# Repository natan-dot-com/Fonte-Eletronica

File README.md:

# Fonte de Tensão Variável (12V-3V)
## Introdução
Projeto para a aula de Eletrônica para Computação (SSC0180), no ICMC/USP-São Carlos, ministrada pelo docente [Eduardo Simões](https://gitlab.com/simoesusp).
O projeto consiste numa fonte de alimentação de tensão variável, feita num simulador com o uso de resistores, diodos, capacitores, transformadores e um regulador de tensão.

O circuito fora feito pelo grupo 9 de 2020/1:  
- [Natan Sanches](https://github.com/natan-dot-com);  
- [Gabriel Vicente Rodrigues](https://github.com/gabriel-vr);  
- [Lucas Mihara](https://github.com/lucasmihara);  
- [Vitor Beneti Martins](https://github.com/benetche).  

Projeto indexado ao [Gitlab](https://gitlab.com/simoesusp/disciplinas/-/tree/master/SSC0180-Eletronica-para-Computacao).

## Sobre o projeto
O projeto, por medidas de restrição social, fora feito em dois simuladores de circuitos elétricos: no [Falstad](http://tinyurl.com/y9k5xbtm), online, e no Eagle, outro simulador mais completo que também executa a impressão da placa de circuito final. As imagens e o arquivo do projeto estão contidos neste repositório e a seguir.  
Houve também a produção de um [vídeo explicativo](https://youtu.be/nBSvIfqxYiY) acerca do projeto, que complementará a leitura dos circuitos.  
### Esquemático - Falstad:

### Esquemático - Eagle:
 
### Placa de circuito - Eagle:

Lista de materiais utilizados:
- 1x Capacitor Eletrolítico 470µF/50V - R$ 0,90
- 1x Diodo Zener 13V/0,5W - R$ 0,09
- 4x Diodo 1N4007 - R$ 0,44 (Substituível por uma ponte retificadora)
- 1x Transistor NPN BC337 - R$ 0,18
- 1x Resistor 1K8 - R$ 0,08
- 2x Resistor 2K2 - R$ 0,16
- 1x Potenciômetro Linear de 5K - R$ 1,09
- 1x LED Difuso Branco - R$ 0,23

CUSTO TOTAL: R$ 3,17

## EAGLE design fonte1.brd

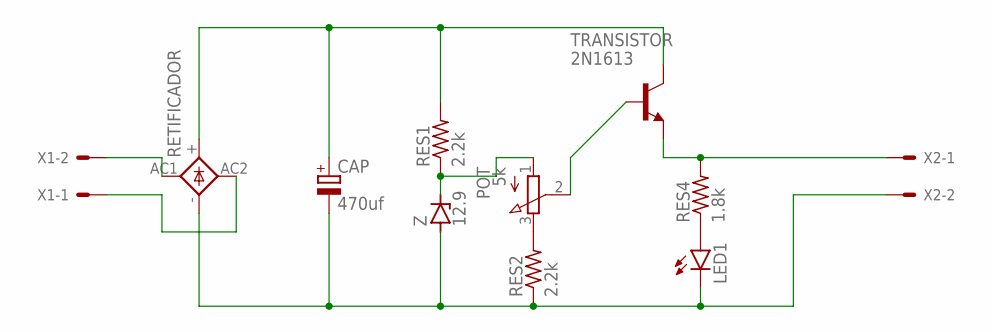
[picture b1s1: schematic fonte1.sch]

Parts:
CAP: 470uf; E3,5-8
LED1: LED3MM
POT: 5k; 3RP/1610N
RES1, RES2: 2.2k; 0207/7
RES4: 1.8k; 0207/7
RETIFICADOR: 1KAB
TRANSISTOR: 2N1613; TO5
X1, X2: KK-156-2
Z: 12.9; C1702-15

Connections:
unnamed: POT.3 (E), RES2.2
unnamed: LED1.A, RES4.1
unnamed: RETIFICADOR.AC1, X1.2
unnamed: RETIFICADOR.AC2, X1.1
unnamed: CAP.+, RES1.2, RETIFICADOR.+, TRANSISTOR.3 (C)
unnamed: CAP.-, LED1.K (C), RES2.1, RETIFICADOR.-, X2.2, Z.A
unnamed: POT.1 (A), RES1.1, Z.C
unnamed: POT.2 (S), TRANSISTOR.2 (B)
unnamed: RES4.2, TRANSISTOR.1 (E), X2.1

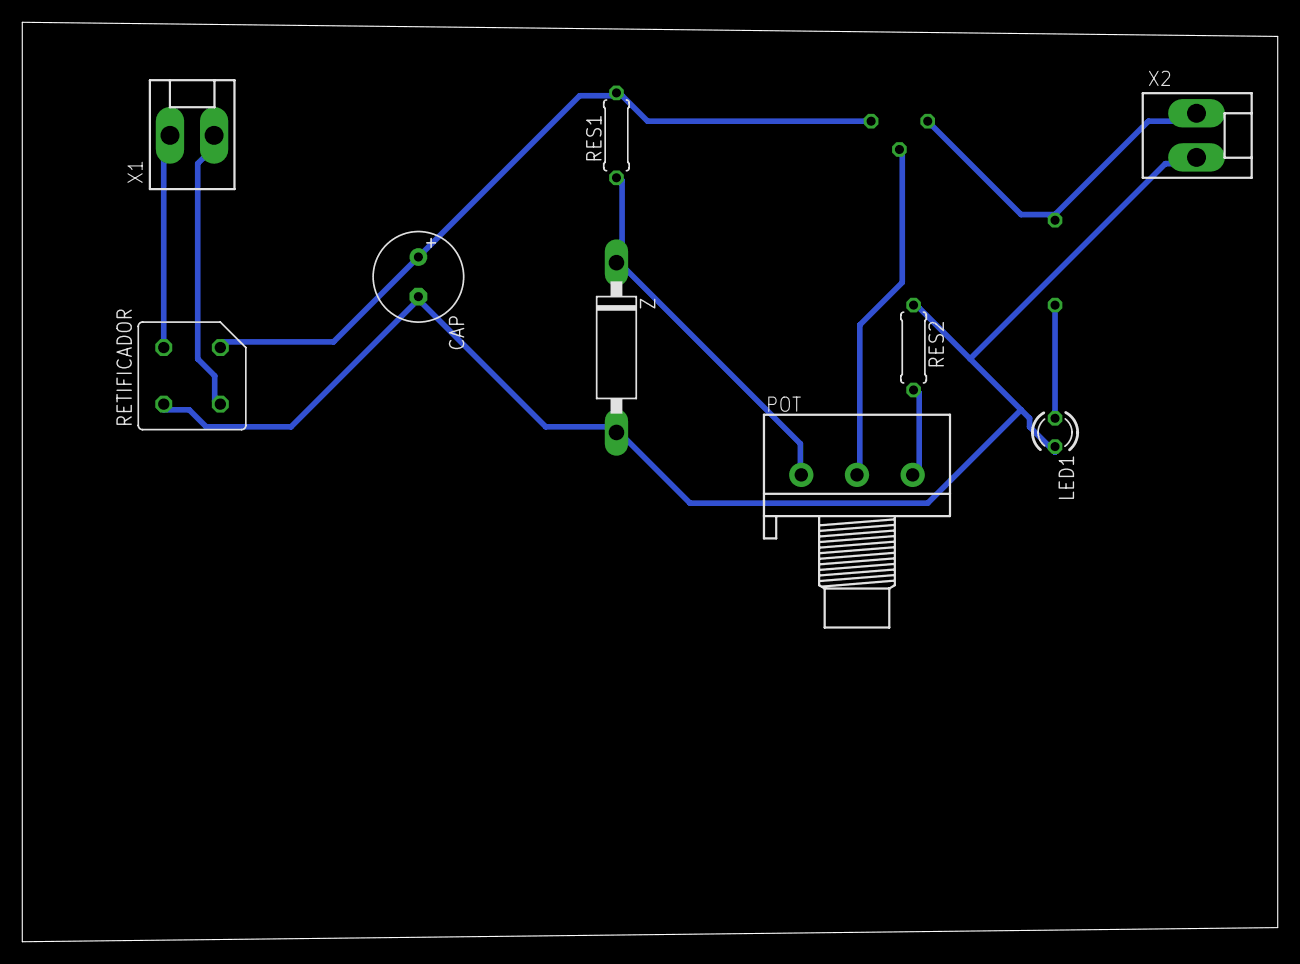
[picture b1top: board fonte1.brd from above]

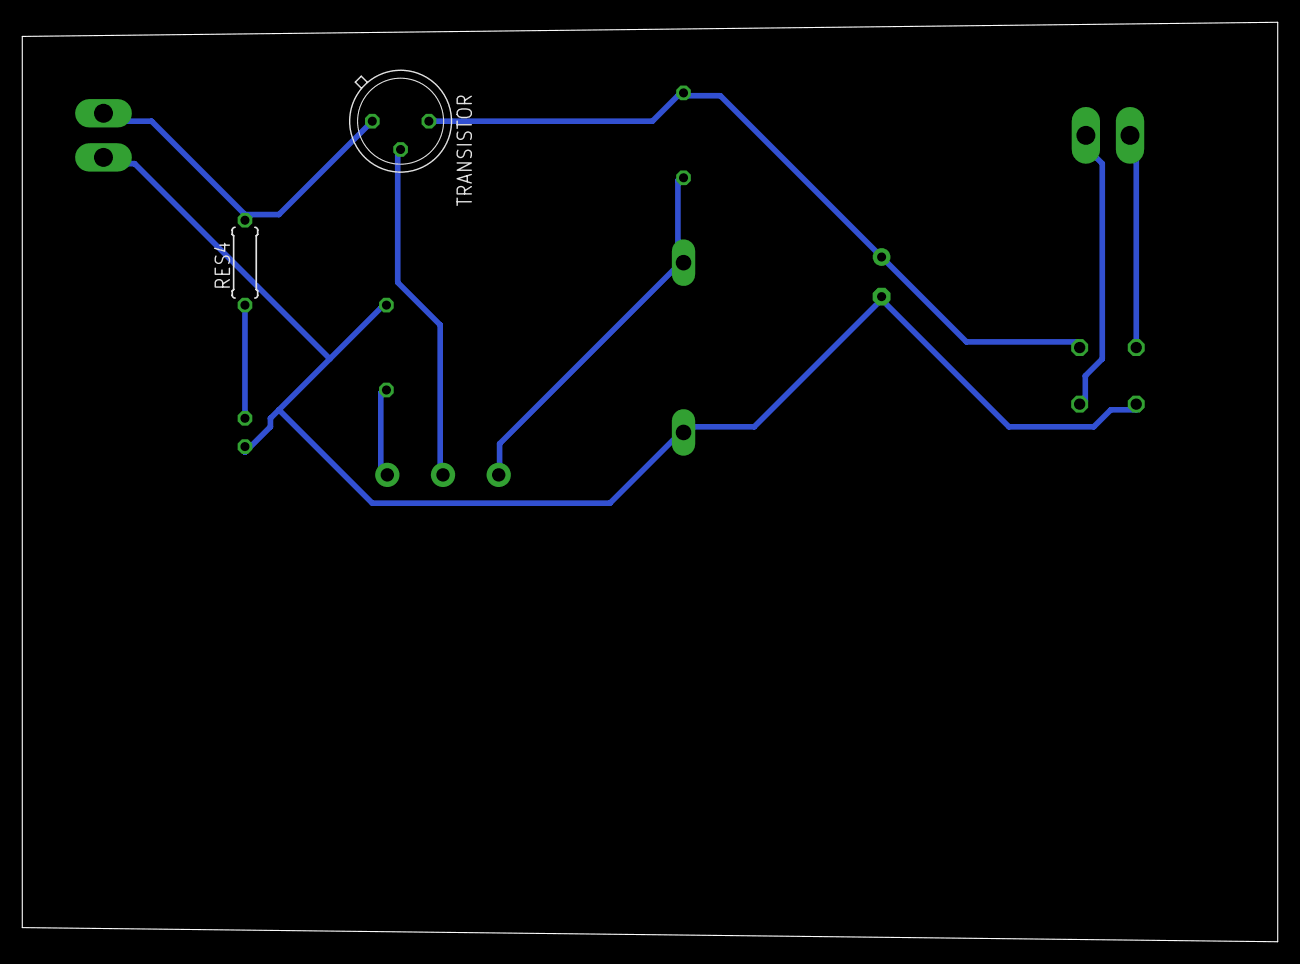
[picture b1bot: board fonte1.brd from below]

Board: 2 copper layers, 112.7 x 82.5 mm, 11 parts (2 on the bottom side), 9 nets.

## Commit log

2020-06-07 Rename circuit-20200607-1629.circuitjs.txt to Fonte - Lucas Mihara (Falstad).txt
2020-06-07 Fonte-Gabriel Vicente
2020-06-07 Rename circuit-20200607-1644.circuitjs.txt to Fonte-Gabriel Vicente
